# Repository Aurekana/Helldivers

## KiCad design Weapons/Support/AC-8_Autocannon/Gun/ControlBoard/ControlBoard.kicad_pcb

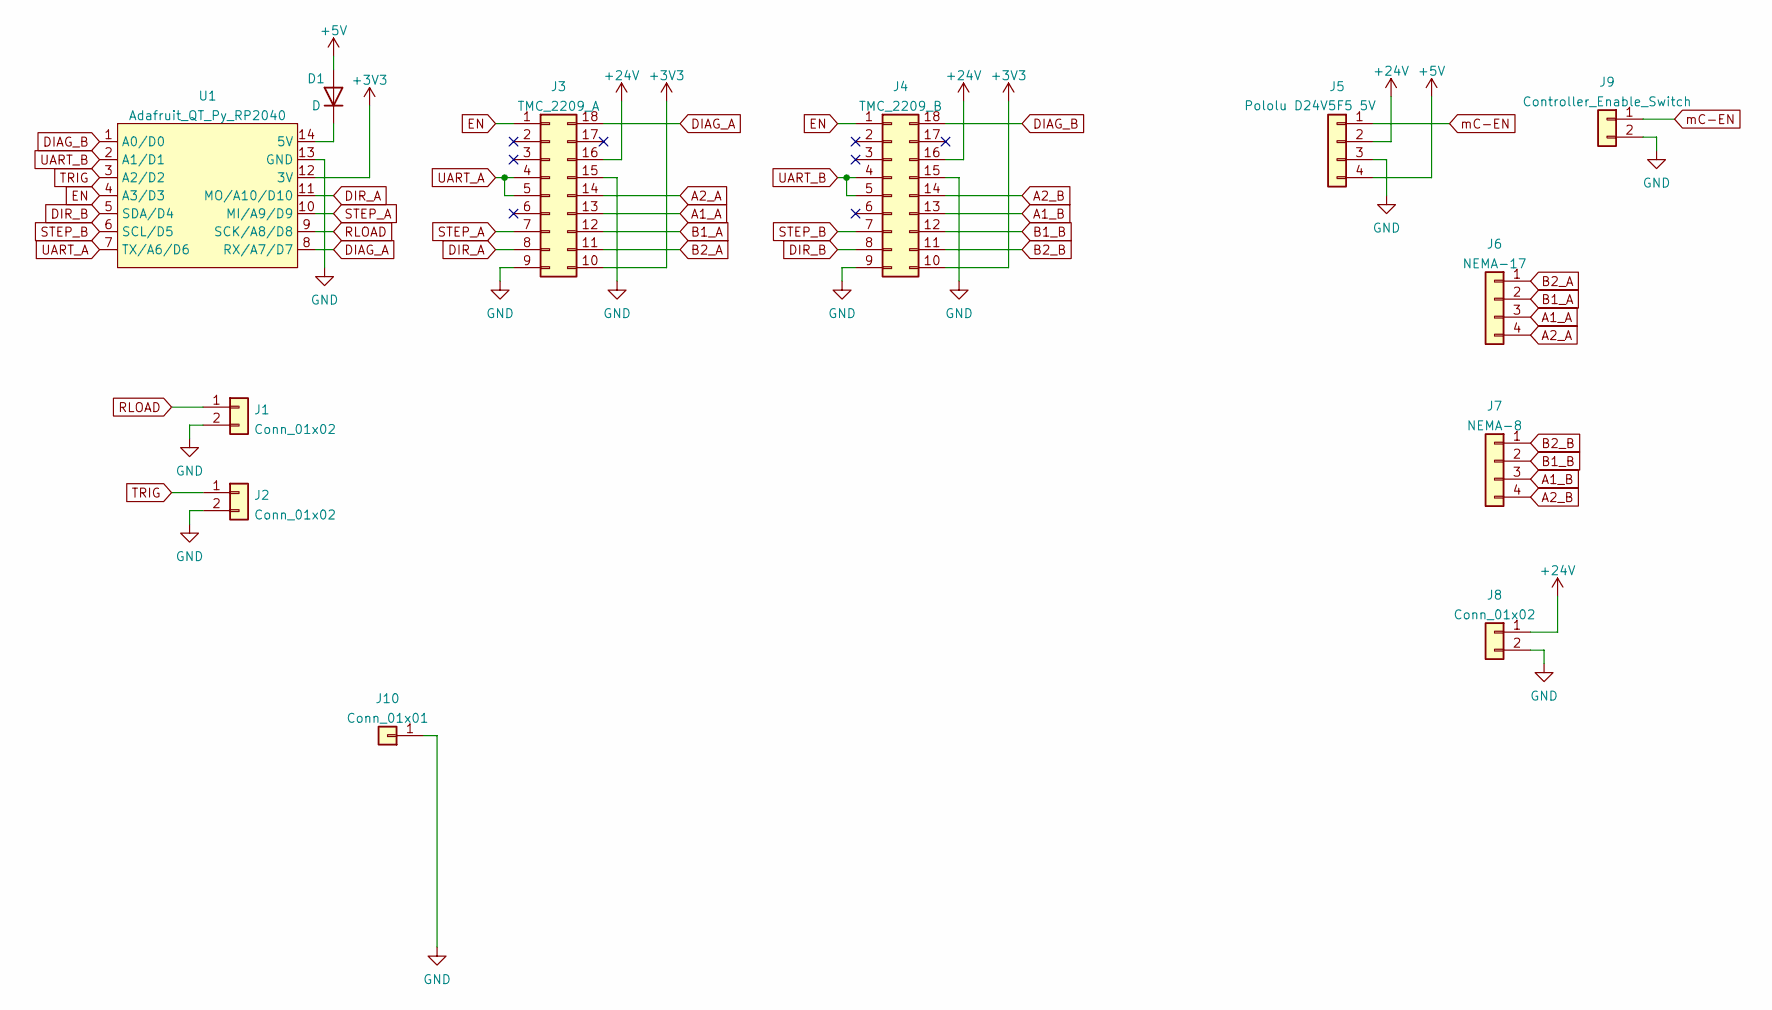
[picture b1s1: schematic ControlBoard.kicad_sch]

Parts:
D1: D; D_0603_1608Metric_Pad1.05x0.95mm_HandSolder
J1, J2: Conn_01x02; JST_PH_B2B-PH-K_1x02_P2.00mm_Vertical
J3: TMC_2209_A; BTT_TMC_2209
J4: TMC_2209_B; BTT_TMC_2209
J5: Pololu D24V5F5 5V; PinHeader_1x04_P2.54mm_Vertical
J6: NEMA-17; PinHeader_1x04_P2.54mm_Vertical
J7: NEMA-8; PinHeader_1x04_P2.54mm_Vertical
J8: Conn_01x02; Molex_KK-396_A-41791-0002_1x02_P3.96mm_Vertical
J9: Controller_Enable_Switch; JST_PH_B2B-PH-K_1x02_P2.00mm_Vertical
J10: Conn_01x01; MountingHole_3.2mm_M3
U1: Adafruit_QT_Py_RP2040; Adafruit_QT_Py_SMD

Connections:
+3V3: J3.10, J4.10, U1.12 (3V)
+5V: D1.2 (A), J5.4
+24V: J3.16, J4.16, J5.2, J8.1
A1_A: J3.13, J6.3
A1_B: J4.13, J7.3
A2_A: J3.14, J6.4
A2_B: J4.14, J7.4
B1_A: J3.12, J6.2
B1_B: J4.12, J7.2
B2_A: J3.11, J6.1
B2_B: J4.11, J7.1
DIAG_A: J3.18, U1.8 (RX/A7/D7)
DIAG_B: J4.18, U1.1 (A0/D0)
DIR_A: J3.8, U1.11 (MO/A10/D10)
DIR_B: J4.8, U1.5 (SDA/D4)
EN: J3.1, J4.1, U1.4 (A3/D3)
GND: J1.2, J2.2, J3.9, J3.15, J4.9, J4.15, J5.3, J8.2, J9.2, J10.1, U1.13 (GND)
unnamed: D1.1 (K), U1.14 (5V)
RLOAD: J1.1, U1.9 (SCK/A8/D8)
STEP_A: J3.7, U1.10 (MI/A9/D9)
STEP_B: J4.7, U1.6 (SCL/D5)
TRIG: J2.1, U1.3 (A2/D2)
UART_A: J3.4, J3.5, U1.7 (TX/A6/D6)
UART_B: J4.4, J4.5, U1.2 (A1/D1)
mC-EN: J5.1, J9.1

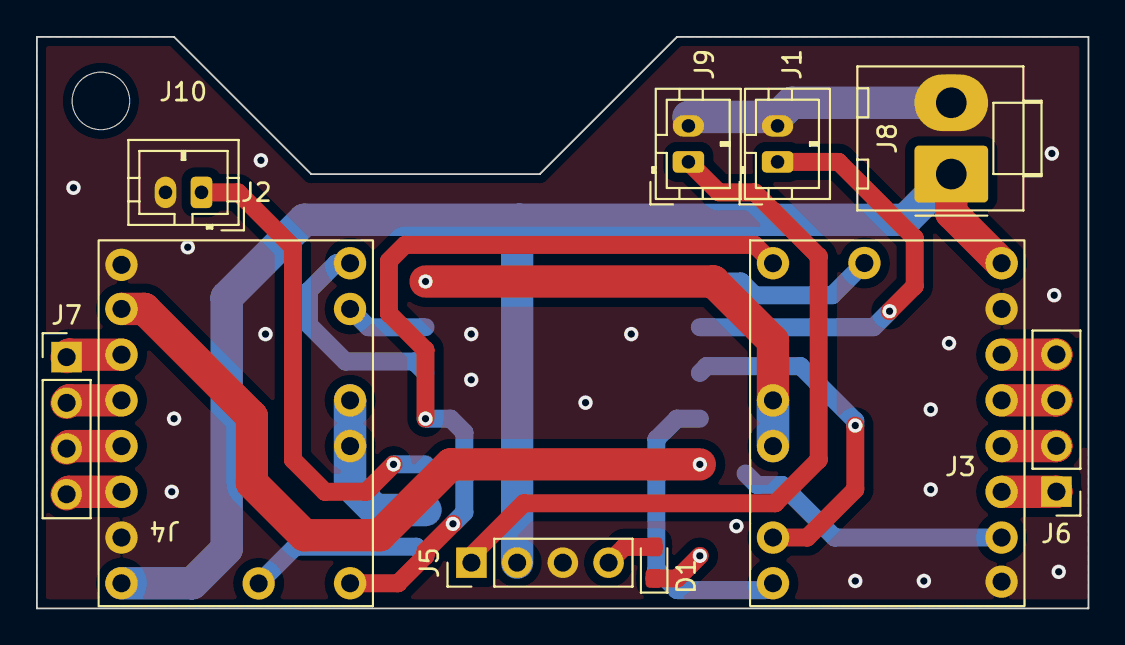
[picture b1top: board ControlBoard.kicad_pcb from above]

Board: 2 copper layers, 58.4 x 31.8 mm, 12 parts (1 on the bottom side), 25 nets.

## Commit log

2024-03-05 Added files
2024-03-06 Added Autocannon mesh
2024-03-08 Updated blend
2024-03-11 Updated files
2024-03-15 Meshed meshes
2024-03-22 Added geometry
2024-03-22 Removed meshes
2024-03-22 Updated Recoilless
2024-03-22 Cleanup
2024-03-27 Processed Meshs
2024-03-30 Updated meshes
2025-02-09 Upodates
2025-03-21 Autocannon Updates
